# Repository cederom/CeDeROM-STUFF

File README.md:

CeDeROM's STUFF
===============

You will find some of my projects related stuff that may be useful for you as well. Use at your own risk. Have fun! =)

Visit my personal website for more information: https://www.tomek.cedro.info.

Visit my company website for contact and pricing: www.cederom.io.

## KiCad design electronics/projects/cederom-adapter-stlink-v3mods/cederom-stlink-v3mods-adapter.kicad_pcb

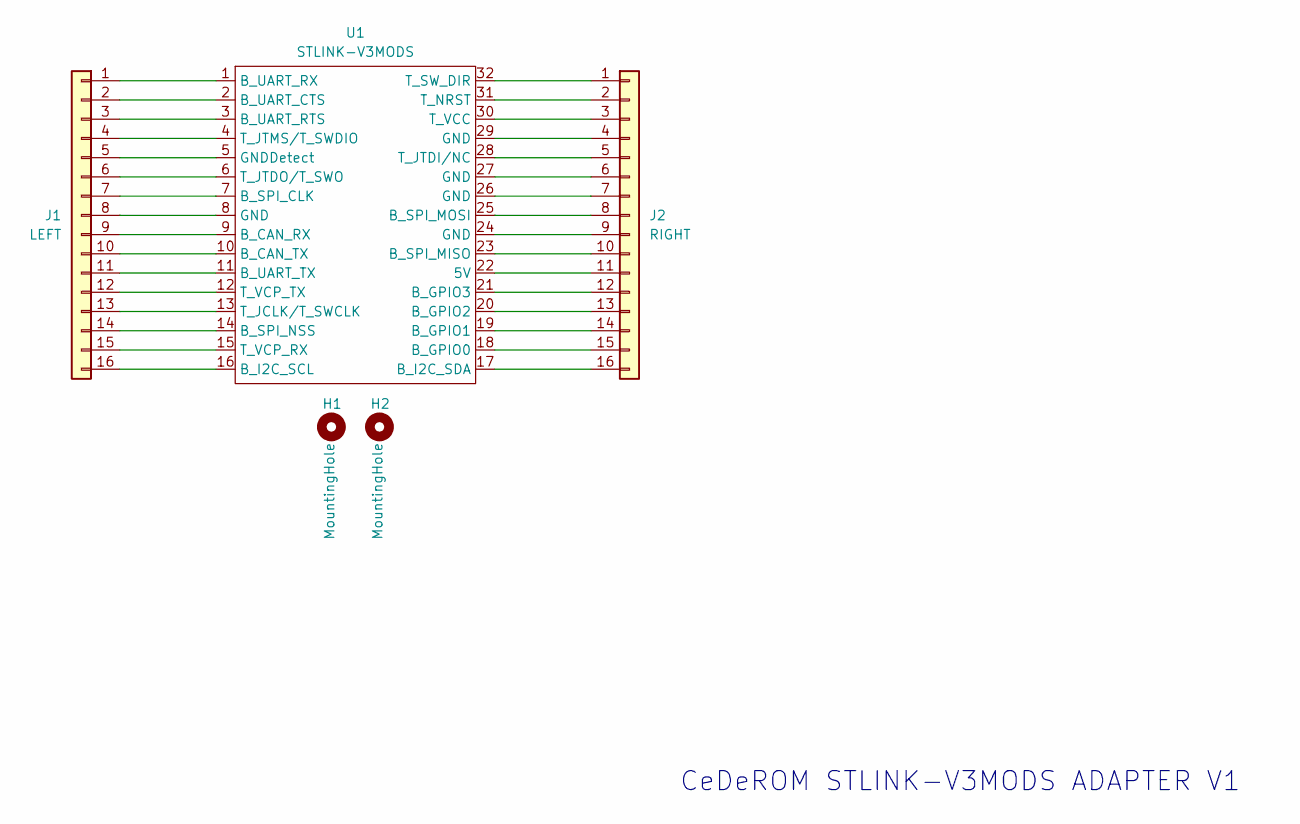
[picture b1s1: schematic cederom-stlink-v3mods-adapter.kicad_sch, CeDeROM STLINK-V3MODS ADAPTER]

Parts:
H1, H2: MountingHole; MountingHole_3.2mm_M3
J1: LEFT; PinHeader_2x08_P2.54mm_Vertical
J2: RIGHT; PinHeader_2x08_P2.54mm_Vertical
U1: STLINK-V3MODS

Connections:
unnamed: J1.1, U1.1 (B_UART_RX)
unnamed: J1.2, U1.2 (B_UART_CTS)
unnamed: J1.3, U1.3 (B_UART_RTS)
unnamed: J1.4, U1.4 (T_JTMS/T_SWDIO)
unnamed: J1.5, U1.5 (GNDDetect)
unnamed: J1.6, U1.6 (T_JTDO/T_SWO)
unnamed: J1.7, U1.7 (B_SPI_CLK)
unnamed: J1.8, U1.8 (GND)
unnamed: J1.9, U1.9 (B_CAN_RX)
unnamed: J1.10, U1.10 (B_CAN_TX)
unnamed: J1.11, U1.11 (B_UART_TX)
unnamed: J1.12, U1.12 (T_VCP_TX)
unnamed: J1.13, U1.13 (T_JCLK/T_SWCLK)
unnamed: J1.14, U1.14 (B_SPI_NSS)
unnamed: J1.15, U1.15 (T_VCP_RX)
unnamed: J1.16, U1.16 (B_I2C_SCL)
unnamed: J2.1, U1.32 (T_SW_DIR)
unnamed: J2.2, U1.31 (T_NRST)
unnamed: J2.3, U1.30 (T_VCC)
unnamed: J2.4, U1.29 (GND)
unnamed: J2.5, U1.28 (T_JTDI/NC)
unnamed: J2.6, U1.27 (GND)
unnamed: J2.7, U1.26 (GND)
unnamed: J2.8, U1.25 (B_SPI_MOSI)
unnamed: J2.9, U1.24 (GND)
unnamed: J2.10, U1.23 (B_SPI_MISO)
unnamed: J2.11, U1.22 (5V)
unnamed: J2.12, U1.21 (B_GPIO3)
unnamed: J2.13, U1.20 (B_GPIO2)
unnamed: J2.14, U1.19 (B_GPIO1)
unnamed: J2.15, U1.18 (B_GPIO0)
unnamed: J2.16, U1.17 (B_I2C_SDA)

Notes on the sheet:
CeDeROM STLINK-V3MODS ADAPTER V1

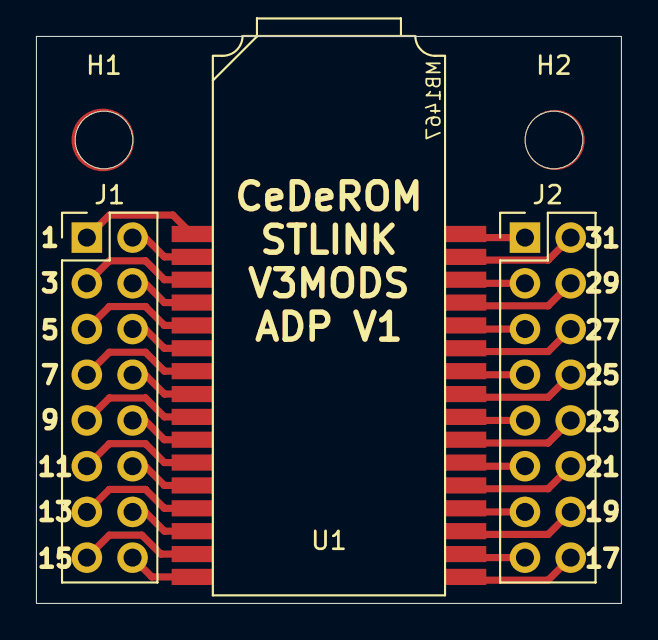
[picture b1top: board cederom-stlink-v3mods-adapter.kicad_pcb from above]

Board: 2 copper layers, 32.5 x 31.5 mm, 5 parts (0 on the bottom side), 32 nets.

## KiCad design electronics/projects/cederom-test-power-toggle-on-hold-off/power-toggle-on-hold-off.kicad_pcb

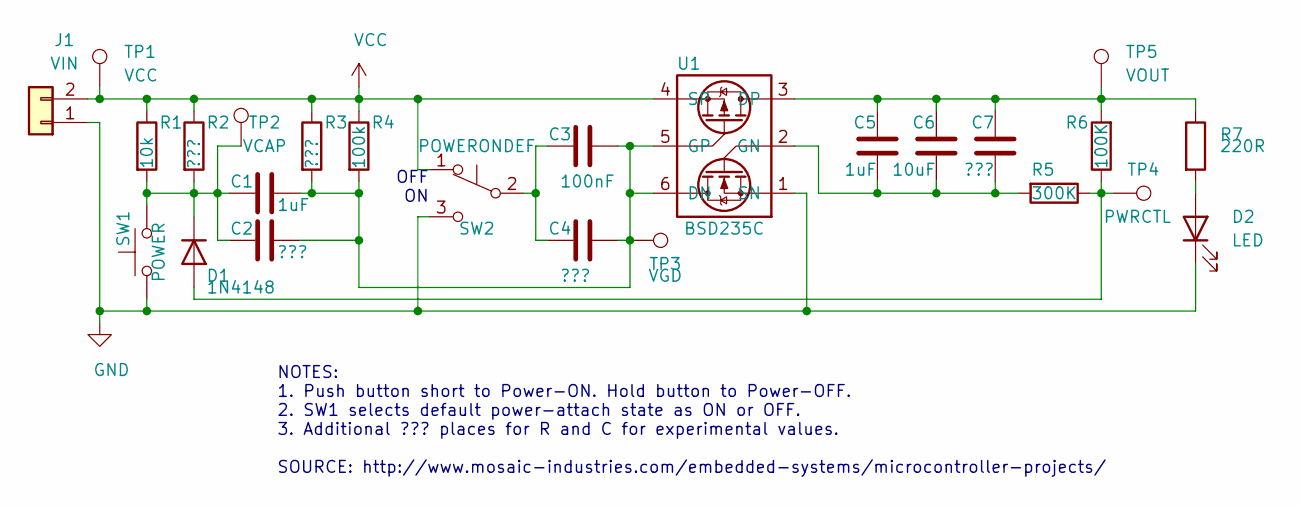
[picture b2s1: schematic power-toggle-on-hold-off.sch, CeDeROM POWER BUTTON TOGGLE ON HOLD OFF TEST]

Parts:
C1, C5: 1uF; C_0805_2012Metric_Pad1.15x1.40mm_HandSolder
C2, C4, C7: ???; C_0805_2012Metric_Pad1.15x1.40mm_HandSolder
C3: 100nF; C_0805_2012Metric_Pad1.15x1.40mm_HandSolder
C6: 10uF; C_0805_2012Metric_Pad1.15x1.40mm_HandSolder
D1: 1N4148; D_0805_2012Metric
D2: LED; D_0805_2012Metric_Pad1.15x1.40mm_HandSolder
J1: VIN; PinHeader_1x02_P2.54mm_Vertical
R1: 10k; R_0603_1608Metric_Pad1.05x0.95mm_HandSolder
R2, R3: ???; R_0603_1608Metric_Pad1.05x0.95mm_HandSolder
R4: 100k; R_0603_1608Metric_Pad1.05x0.95mm_HandSolder
R5: 300K; R_0603_1608Metric_Pad1.05x0.95mm_HandSolder
R6: 100K; R_0603_1608Metric_Pad1.05x0.95mm_HandSolder
R7: 220R; R_0603_1608Metric_Pad1.05x0.95mm_HandSolder
SW1: POWER; SW_SPST_B3U-3000P
SW2: POWERONDEF; SolderJumper-3_P1.3mm_Bridged12_RoundedPad1.0x1.5mm_NumberL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
TP1: VCC; TestPoint_Pad_D2.0mm
TP2: VCAP; TestPoint_Pad_D2.0mm
TP3: VGD; TestPoint_Pad_D2.0mm
TP4: PWRCTL; TestPoint_Pad_D2.0mm
TP5: VOUT; TestPoint_Pad_D2.0mm
U1: BSD235C; SOT-363_SC-70-6_Handsoldering

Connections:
GND: D2.1 (K), J1.1, SW1.1, SW2.3 (C), U1.1 (SN)
unnamed: C1.1, C2.1, C3.1, C4.1, R3.2, R4.2, TP3.1, U1.5 (GP), U1.6 (DN)
unnamed: C1.2, C2.2, D1.1 (K), R1.2, R2.2, SW1.2, TP2.1
unnamed: C3.2, C4.2, SW2.2 (B)
unnamed: C5.1, C6.1, C7.1, R5.2, U1.2 (GN)
unnamed: C5.2, C6.2, C7.2, R6.2, R7.1, TP5.1, U1.3 (DP)
unnamed: D1.2 (A), R5.1, R6.1, TP4.1
unnamed: D2.2 (A), R7.2
VCC: J1.2, R1.1, R2.1, R3.1, R4.1, SW2.1 (A), TP1.1, U1.4 (SP)

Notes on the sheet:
OFF ON
NOTES: 1. Push button short to Power-ON. Hold button to Power-OFF. 2. SW1 selects default power-attach state as ON or OFF. 3. Additional ??? places for R and C for experimental values. SOURCE: http://www.mosaic-industries.com/embedded-systems/microcontroller-projects/

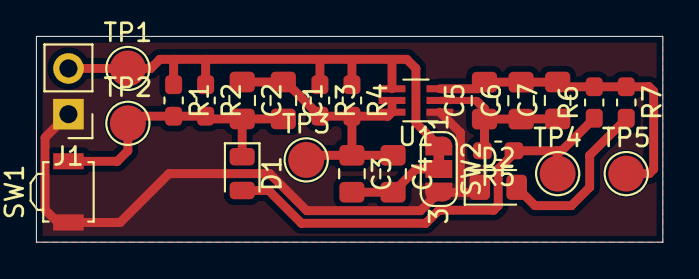
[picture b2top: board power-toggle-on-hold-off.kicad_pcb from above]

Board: 2 copper layers, 34.8 x 11.4 mm, 25 parts (0 on the bottom side), 9 nets.

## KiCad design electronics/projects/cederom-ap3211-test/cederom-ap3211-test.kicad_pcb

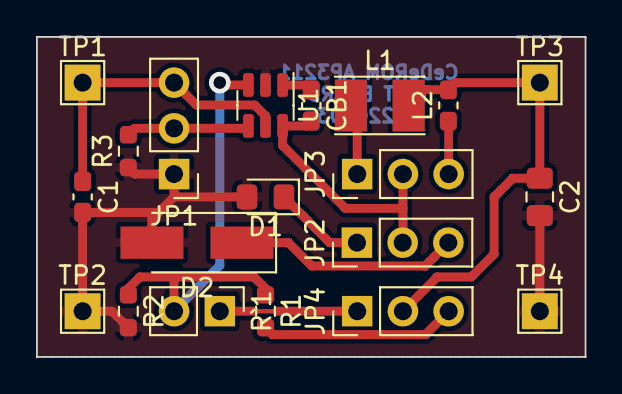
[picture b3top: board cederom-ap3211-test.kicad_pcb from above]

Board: 2 copper layers, 30.5 x 17.8 mm, 20 parts (0 on the bottom side), 13 nets.

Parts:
C1: 10uF/25V; C_0603_1608Metric_Pad1.08x0.95mm_HandSolder
C2: 22uF/6.3V; C_0805_2012Metric_Pad1.18x1.45mm_HandSolder
CB1: 10nF; C_0603_1608Metric_Pad1.08x0.95mm_HandSolder
D1: 1N4148; D_0805_2012Metric_Pad1.15x1.40mm_HandSolder
D2: B140-E3/61T; D_SMA_Handsoldering
JP1: EN; PinHeader_1x03_P2.54mm_Vertical
JP2: DSEL; PinHeader_1x03_P2.54mm_Vertical
JP3: LSEL; PinHeader_1x03_P2.54mm_Vertical
JP4: RSEL; PinHeader_1x03_P2.54mm_Vertical
L1: 4.7uH; L_Taiyo-Yuden_NR-30xx_HandSoldering
L2: 4.7uH; L_0603_1608Metric_Pad1.05x0.95mm_HandSolder
R1: 49.9k; R_0603_1608Metric_Pad0.98x0.95mm_HandSolder
R2: 16.3k; R_0603_1608Metric_Pad0.98x0.95mm_HandSolder
R3: 10k; R_0603_1608Metric_Pad0.98x0.95mm_HandSolder
R`1: VAR; PinHeader_1x02_P2.54mm_Vertical
TP1: VIN; TestPoint_THTPad_2.0x2.0mm_Drill1.0mm
TP2, TP4: GND; TestPoint_THTPad_2.0x2.0mm_Drill1.0mm
TP3: VOUT; TestPoint_THTPad_2.0x2.0mm_Drill1.0mm
U1: AP3211; SOT-23-6

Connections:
GND: C1.2, C2.2, D1.2 (A), D2.2 (A), JP1.1 (A), R2.2, R3.1, TP2.1, TP4.1, U1.2 (GND)
unnamed: C1.1, JP1.3 (B), TP1.1, U1.5 (IN)
unnamed: C2.1, JP4.2 (C), L1.2, L2.2, TP3.1
unnamed: CB1.1, U1.1 (BS)
unnamed: CB1.2, JP2.2 (C), JP3.2 (C), U1.6 (SW)
unnamed: D1.1 (K), JP2.1 (A)
unnamed: D2.1 (K), JP2.3 (B)
unnamed: JP1.2 (C), R3.2, U1.4 (EN)
unnamed: JP3.1 (A), L1.1
unnamed: JP3.3 (B), L2.1
unnamed: JP4.1 (A), R`1.1
unnamed: JP4.3 (B), R1.2
unnamed: R1.1, R2.1, R`1.2, U1.3 (FB)

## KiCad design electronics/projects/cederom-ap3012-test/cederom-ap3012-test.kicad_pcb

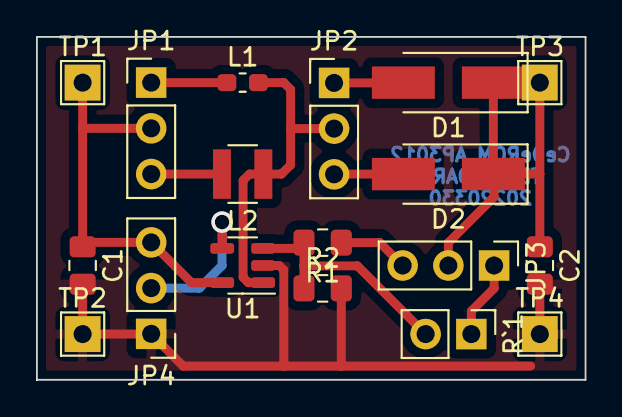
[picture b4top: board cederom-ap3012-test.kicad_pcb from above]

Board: 2 copper layers, 30.5 x 19.1 mm, 18 parts (0 on the bottom side), 12 nets.

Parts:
C1, C2: 1uF; C_0805_2012Metric_Pad1.18x1.45mm_HandSolder
D1: STPS1L40A; D_SMA_Handsoldering
D2: B140-E3/61T; D_SMA_Handsoldering
JP1: LSEL; PinHeader_1x03_P2.54mm_Vertical
JP2: DSEL; PinHeader_1x03_P2.54mm_Vertical
JP3: RSEL; PinHeader_1x03_P2.54mm_Vertical
JP4: !SHDN; PinHeader_1x03_P2.54mm_Vertical
L1: 10uH; L_0603_1608Metric_Pad1.05x0.95mm_HandSolder
L2: 10uH; L_Abracon_ASPI-3012S
R1, R2: C_0805_2012Metric_Pad1.18x1.45mm_HandSolder
R`1: VAR; PinHeader_1x02_P2.54mm_Vertical
TP1: VIN; TestPoint_THTPad_2.0x2.0mm_Drill1.0mm
TP2, TP4: GND; TestPoint_THTPad_2.0x2.0mm_Drill1.0mm
TP3: VOUT; TestPoint_THTPad_2.0x2.0mm_Drill1.0mm
U1: AP3012; SOT-23-5

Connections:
GND: C1.2, C2.2, JP4.1 (A), R2.2, TP2.1, TP4.1, U1.2 (GND)
unnamed: C1.1, JP1.2 (C), JP4.3 (B), TP1.1, U1.5 (IN)
unnamed: C2.1, D1.1 (K), D2.1 (K), JP3.2 (C), TP3.1
unnamed: D1.2 (A), JP2.1 (A)
unnamed: D2.2 (A), JP2.3 (B)
unnamed: JP1.1 (A), L1.1
unnamed: JP1.3 (B), L2.1
unnamed: JP2.2 (C), L1.2, L2.2, U1.1 (SW)
unnamed: JP3.1 (A), R`1.1
unnamed: JP3.3 (B), R1.1
unnamed: JP4.2 (C), U1.4 (~SHDN)
unnamed: R1.2, R2.1, R`1.2, U1.3 (FB)

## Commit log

2014-11-16 README, first commit
2014-11-16 3D: Added Zmorph3D firmware section and files.
2014-11-16 3D: Added Zmorph3D old firmwares and config.
2014-11-16 3D: Added Zmorph3D config for Cura slicer.
2014-11-24 3D: Updated Zmorph3D config (support/base/wall/fill).
2021-02-19 Added KiCAD libraries.
2021-02-19 Added SPICE models from Diodes Inc.
2021-02-19 Added simple vias and track width test board.
2021-02-19 Added power toggle circuit idea. Not yet operational!
2021-02-19 Added KiCAD SPICE library submodule.
2021-02-19 Added Spartan Edge Accelerator Board stuff (Spartan7+ESP32).
2021-02-19 Readme update.
2021-02-23 Locations rename.
2021-02-23 SEA Board XDC updates.
2021-04-09 DIY / DSO QUAD Mini Oscilloscope accumulator replacement.
2021-04-14 Added "Building a RISC-V CPU Core" submodule.
2021-04-14 Added "RISC-V_MYTH_Workshop" submodule.
2021-04-14 Renamed RISC-V tutorials to examples.
2021-04-14 Added "vivado-risc-v" submodule by eugene-tarassov.
2021-04-14 Added "CVA6 RISC-V CPU" from OpenHW Group.
2021-04-14 Added "Rocket Chip Generator for RISC-V Rocket Core" from Chips Alliance.
2021-04-14 Added "xilinx-risc-v" by irmo with PicoRV.
2021-05-07 zvenvsdk.sh sctipt automates work with ZEPHYR RTOS + Python VirtualEnv.
2021-05-09 VENVSDK: Detect local Zephyr + venv shell only options.
    * Script can now detect local .west provided zephyr installation.
    * New 'venv' parameter to spawn venv only (no ZephyrSDK) useful for testing.
2021-07-14 zvenvsdk.sh script now supports Zephyr for ARM and ESP32.
2021-08-27 Some useful cheatsheets.
2022-01-16 Updated zvenvsdk.sh script.
2022-01-16 Added "Pro Git" by Scott Chacon and Ben Straub book PDF.
    * Book is free to read and download from https://git-scm.com/book/en/v2.
2022-01-16 Added ANSI Escape Codes cheatsheet by https://github.com/fnky.
2022-02-27 Added ASCII table and ASCII and UNICODE cheatsheet.
2022-04-01 AP3012 dc-dc step-up test board prototype added.
2022-04-02 * e/libs -> e/lib. * Updated KiCAD symbol format to KiCAD 6. * Added AP3211 symbol. * Added ESP32-C3-WROOM-02 footprint.
2022-04-04 Added AP3211 test board prototype.
2022-06-11 Embedded Python Venv helper script updates.
    * Noted its not only for Zephyr anymore (also MicroPython, NuttX, etc).
    * Also installs esptool, mpremote, etc, for ESP32.
    * Fixed init copy/diff/check.
2022-06-11 Added GitHub GIT Cheatscheet.
2022-06-11 Added unix/freebsd/Sierra LTE modem notes.
2022-09-13 Added my FreeBSD ports.
2022-10-02 Added FreeBSD Port comms/hackrf version 2017.02.1 before update.
2022-10-02 FreeBSD/ports/comms/hackrf: Update port to 2021.03.1 version.
    * 2022.09.1 needs LibUSB call that is not yet in the release.
2022-10-05 FreeBSD/ports/comms/hackrf: 2021.03.1 -> 2021.03.1_1 (libfftw3f).
2023-03-18 Added KiCAD symbol: STM-25-31.
2023-03-18 Renamed KiCAD sym and fpn libs to short name CeDeROM.
2023-03-18 Added pictured periodic table chemistry cheatsheet.
2023-03-18 Added color resistor table and wheel cheatsheet.
2023-03-18 Added screw size table cheatsheet.
2023-03-18 Added x64 asm+reg cheatsheet.
2023-03-18 Added KiCAD sym+ftprnt Filter_QLT_FYF10T6.
2023-03-18 Added KiCAD footprint DegsonElectronics DG212R.
2023-03-18 KiCAD: FYF10T6 footprint fixup.
2023-06-04 Updated Filter_QLT_FYF10T6 KiCAD footprint after practical verification.
2023-06-04 Added AQY214S KiCAD symbol.
2023-06-04 KiCAD/PCB: Added SOP-4_6.0x2.54mm_P1.2x0.8mm footprint.
2023-06-04 KiCAD/PCB: Added Transformer_INDEL_TEZ-38x45 footprint.
2024-03-11 Add new reference on EM7305 modem.
    * http://netlab.dhis.org/wiki/hardware:huawei:e3272
2024-04-28 Update evenvsdk.sh python venv script.
    * Added separate variable to store Python version to use.
    * Fixed script init command / overwrite / update part.
2024-06-30 evenvsdk.sh now supports ESP IDF.
    * Syntax changed a bit.
    * Now runs into python venv only by default.
    * Use 'zephyr' or 'esp' parameter when working with those SDK.
    * ESP IDF default bootstrap fails on FreeBSD. Make workarounds to use it here.
2024-06-30 evenvsdk.sh fixes.
    * Fix pwd/cwd (stay in dir where called from).
    * Fix python dependencies.
2024-08-05 Fix evenvsdk.sh updating itself.
2024-08-05 evenvsdk.sh add python version variable.
2024-10-27 embedded/nuttx: Add release build/run helper scripts.
2024-11-24 3D: Added CeDeROM USB HUB i-Tec U3CHARGEHUB16 HOLDER.
    Also published at:
    * https://makerworld.com/en/models/815133#profileId-757223
    * https://thangs.com/designer/cederom/3d-model/CeDeROM_USB_HUB_i-Tec_U3CHARGEHUB16_HOLDER-1207182
2025-02-22 Add FNIRSI FNB58 USB device descriptors dump.
2025-08-20 e/lib: KiCAD symbol+footprint for STLINK-V3MODS.
2025-08-20 e/lib: KiCAD footprint for centronics 14 pin vertical.
2025-08-20 e: rename prototypes -> projects.
2025-08-20 e: CeDeROM STLINK-V3MODS adapter added (sch+pcd+grb).
2025-08-22 e: rename e/projects prefix test and adapter.
2026-04-19 Added ESP32-S3-LCD-1.28 kicad expansion symbol and footprint.
    https://www.waveshare.com/esp32-s3-lcd-1.28.htm
2026-04-19 Added Doxygen cheatsheet.
2026-04-19 Added ReStructuredText/RST Sphinx cheatsheet.
2026-04-19 Added net socket cheatsheet by tetsuo.
2026-04-19 Added 3d model for panel plug dummy.
2026-04-19 Added 3d replacement ratchet for wheel of fortune toy.
2026-04-19 Added SO24-to-DIP24 adapter project.
2026-04-19 Added April vgb300 USB video grabber descriptors dump.
2026-06-04 lib/kicad: Fix ESP32-S3-Touch-LCD-1.28 symbol and footprint.
